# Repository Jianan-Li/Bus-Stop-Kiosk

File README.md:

# Bus-Stop-Kiosk

Click <a href="http://www.jianan.li/bus-stop-kiosk">here</a> for more info on this project.

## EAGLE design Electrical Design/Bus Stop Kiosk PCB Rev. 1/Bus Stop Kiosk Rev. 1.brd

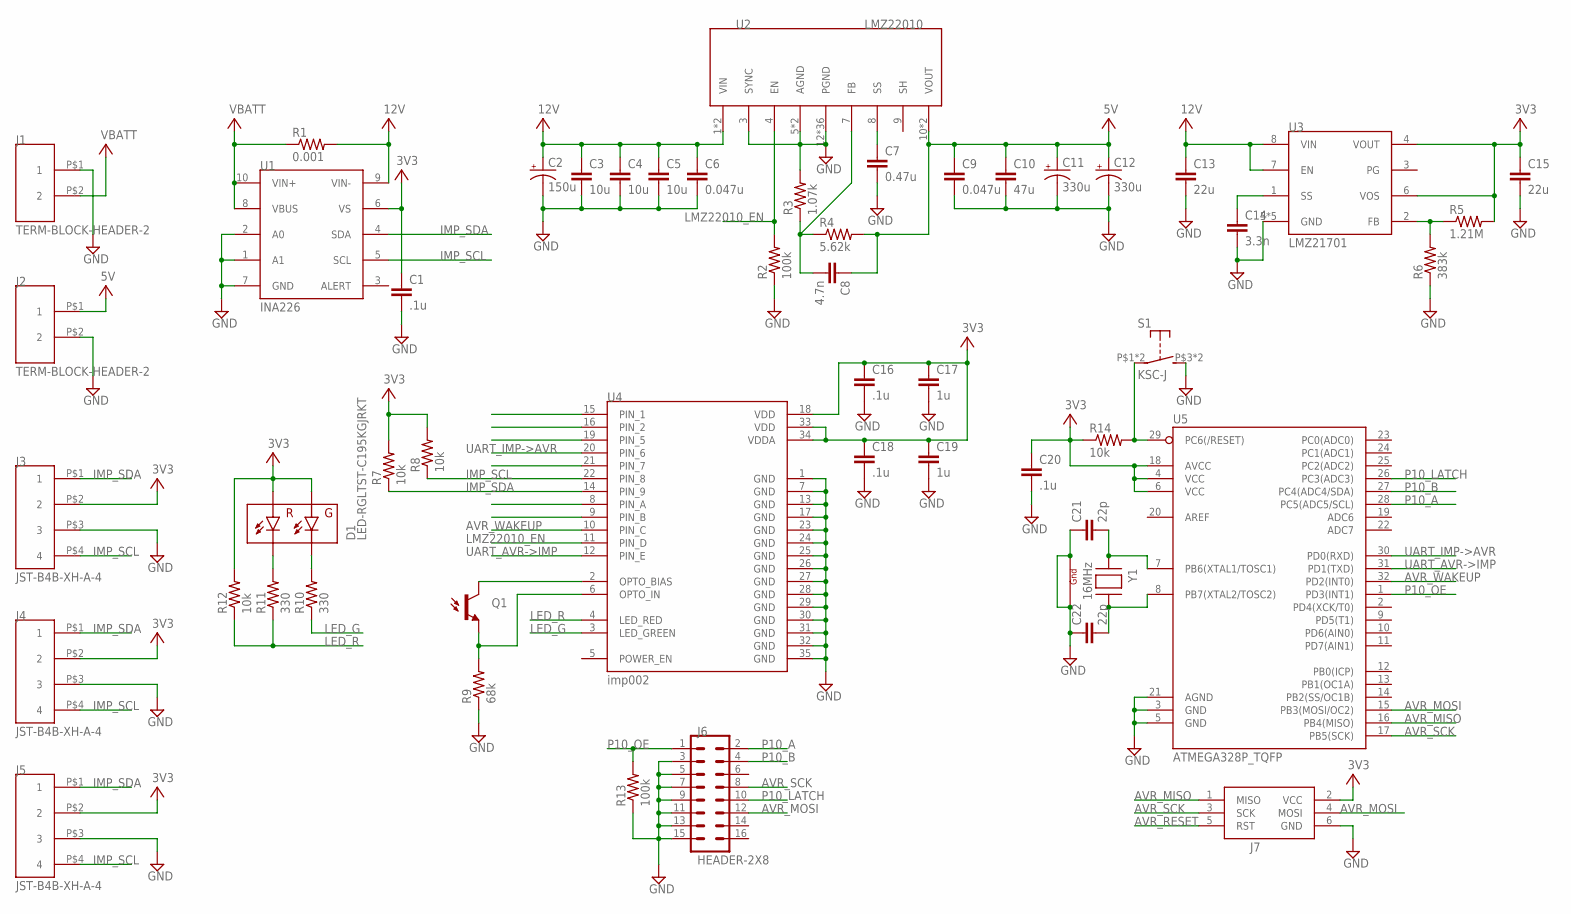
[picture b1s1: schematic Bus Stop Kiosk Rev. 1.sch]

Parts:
C1, C16, C18, C20: .1u; C0603K
C2: 150u; PANASONIC_G
C3, C4, C5: 10u; C1210K
C6, C9: 0.047u; C1206K
C7: 0.47u; C0603K
C8: 4.7n; C0603K
C10: 47u; C1210K
C11, C12: 330u; EIA7343
C13: 22u; C1210K
C14: 3.3n; C0603K
C15: 22u; C0805K
C17, C19: 1u; C0603K
C21, C22: 22p; C0603K
D1: LED-RGLTST-C195KGJRKT; LTST-C195KGJRKT
J1, J2: TERM-BLOCK-HEADER-2; TERM-BLOCK-HDR-2
J3, J4, J5: JST-B4B-XH-A-4
J6: HEADER-2X8; HEADER-2X8-SHROUDED
J7: AVRISP-6; AVRISP
Q1: PHOTOTRANSISTORPT17-21C-L41-TR8; PT17-21C-L41-TR8
R1: 0.001; R1206
R2, R13: 100k; R0603
R3: 1.07k; R0603
R4: 5.62k; R0603
R5: 1.21M; R0603
R6: 383k; R0603
R7, R8, R12, R14: 10k; R0603
R9: 68k; R0603
R10, R11: 330; R0603
S1: KSC-J; C&K-KSC
U1: INA226; VSSOP-10
U2: LMZ22010; TO-PMOD-11
U3: LMZ21701; SIL0008E
U4: imp002; ELECTRIC_IMP_IMP002
U5: ATMEGA328P_TQFP; TQFP32-08
Y1: 16MHz; NX3225

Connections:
3V3: C1.1, C15.1, C16.1, C17.1, C18.1, C19.1, C20.1, D1.P$1 (GA), D1.P$2 (RA), J3.P$2 (2), J4.P$2 (2), J5.P$2 (2), J7.2 (VCC), R5.2, R7.2, R8.2, R12.2, R14.1, U1.6 (VS), U3.4 (VOUT), U3.6 (VOS), U4.18 (VDD), U4.33 (VDD), U4.34 (VDDA), U5.4 (VCC), U5.6 (VCC), U5.18 (AVCC)
5V: C8.1, C9.1, C10.1, C11.A (+), C12.A (+), J2.P$1 (1), R4.2, U2.10 (VOUT), U2.11 (VOUT)
12V: C2.+, C3.1, C4.1, C5.1, C6.1, C13.1, R1.2, U1.9 (VIN-), U2.1 (VIN), U2.2 (VIN), U3.7 (EN), U3.8 (VIN)
ADC1: U4.8 (PIN_A)
ADC2: U4.9 (PIN_B)
AVR_MISO: J7.1 (MISO), U5.16 (PB4(MISO))
AVR_MOSI: J6.12, J7.4 (MOSI), U5.15 (PB3(MOSI/OC2))
AVR_RESET: J7.5 (RST), R14.2, S1.P$1, S1.P$2, U5.29 (PC6(/RESET))
AVR_SCK: J6.8, J7.3 (SCK), U5.17 (PB5(SCK))
AVR_WAKEUP: U4.10 (PIN_C), U5.32 (PD2(INT0))
C21: C21.2, U5.7 (PB6(XTAL1/TOSC1)), Y1.1 (X1)
GND: C1.2, C2.-, C3.2, C4.2, C5.2, C6.2, C7.2, C9.2, C10.2, C11.C (-), C12.C (-), C13.2, C14.2, C15.2, C16.2, C17.2, C18.2, C19.2, C20.2, C21.1, C22.1, J1.P$1 (1), J2.P$2 (2), J3.P$3 (3), J4.P$3 (3), J5.P$3 (3), J6.3, J6.5, J6.7, J6.9, J6.11, J6.13, J6.15, J7.6 (GND), R2.1, R3.2, R6.1, R9.1, R13.1, S1.P$3 (S), S1.P$4 (S), U1.1 (A1), U1.2 (A0), U1.7 (GND), U2.3 (SYNC), U2.5 (AGND), U2.6 (AGND), U2.12 (PGND), U2.P$1 (PGND), U2.P$2 (PGND), U2.P$3 (PGND), U2.P$4 (PGND), U2.P$5 (PGND), U2.P$6 (PGND), U2.P$7 (PGND), U2.P$8 (PGND), U2.P$9 (PGND), U2.P$10 (PGND), U2.P$11 (PGND), U2.P$12 (PGND), U2.P$13 (PGND), U2.P$14 (PGND), U2.P$15 (PGND), U2.P$16 (PGND), U2.P$17 (PGND), U2.P$18 (PGND), U2.P$19 (PGND), U2.P$20 (PGND), U2.P$21 (PGND), U2.P$22 (PGND), U2.P$23 (PGND), U2.P$24 (PGND), U2.P$25 (PGND), U2.P$26 (PGND), U2.P$27 (PGND), U2.P$28 (PGND), U2.P$29 (PGND), U2.P$30 (PGND), U2.P$31 (PGND), U2.P$32 (PGND), U2.P$33 (PGND), U2.P$34 (PGND), U2.P$35 (PGND), U3.5 (GND), U3.9 (GND), U3.10 (GND), U3.11 (GND), U3.12 (GND), U4.1 (GND), U4.7 (GND), U4.13 (GND), U4.17 (GND), U4.23 (GND), U4.24 (GND), U4.25 (GND), U4.26 (GND), U4.27 (GND), U4.28 (GND), U4.29 (GND), U4.30 (GND), U4.31 (GND), U4.32 (GND), U4.35 (GND), U5.3 (GND), U5.5 (GND), U5.21 (AGND), Y1.2 (G2), Y1.4 (G1)
IMP_SCL: J3.P$4 (4), J4.P$4 (4), J5.P$4 (4), R8.1, U1.5 (SCL), U4.22 (PIN_8)
IMP_SDA: J3.P$1 (1), J4.P$1 (1), J5.P$1 (1), R7.1, U1.4 (SDA), U4.14 (PIN_9)
LED_G: R10.1, U4.3 (LED_GREEN)
LED_R: R11.1, R12.1, U4.4 (LED_RED)
LMZ22010_EN: R2.2, U2.4 (EN), U4.11 (PIN_D)
unnamed: Q1.C, U4.2 (OPTO_BIAS)
unnamed: Q1.E, R9.2, U4.6 (OPTO_IN)
unnamed: D1.P$3 (GC), R10.2
unnamed: D1.P$4 (RC), R11.2
unnamed: C14.1, U3.1 (SS)
unnamed: C8.2, R3.1, R4.1, U2.7 (FB)
unnamed: C7.1, U2.8 (SS)
unnamed: R5.1, R6.2, U3.2 (FB)
unnamed: C22.2, U5.8 (PB7(XTAL2/TOSC2)), Y1.3 (X2)
P10_A: J6.2, U5.28 (PC5(ADC5/SCL))
P10_B: J6.4, U5.27 (PC4(ADC4/SDA))
P10_LATCH: J6.10, U5.26 (PC3(ADC3))
P10_OE: J6.1, R13.2, U5.1 (PD3(INT1))
UART_AVR->IMP: U4.12 (PIN_E), U5.31 (PD1(TXD))
UART_IMP->AVR: U4.20 (PIN_6), U5.30 (PD0(RXD))
VBATT: J1.P$2 (2), R1.1, U1.8 (VBUS), U1.10 (VIN+)

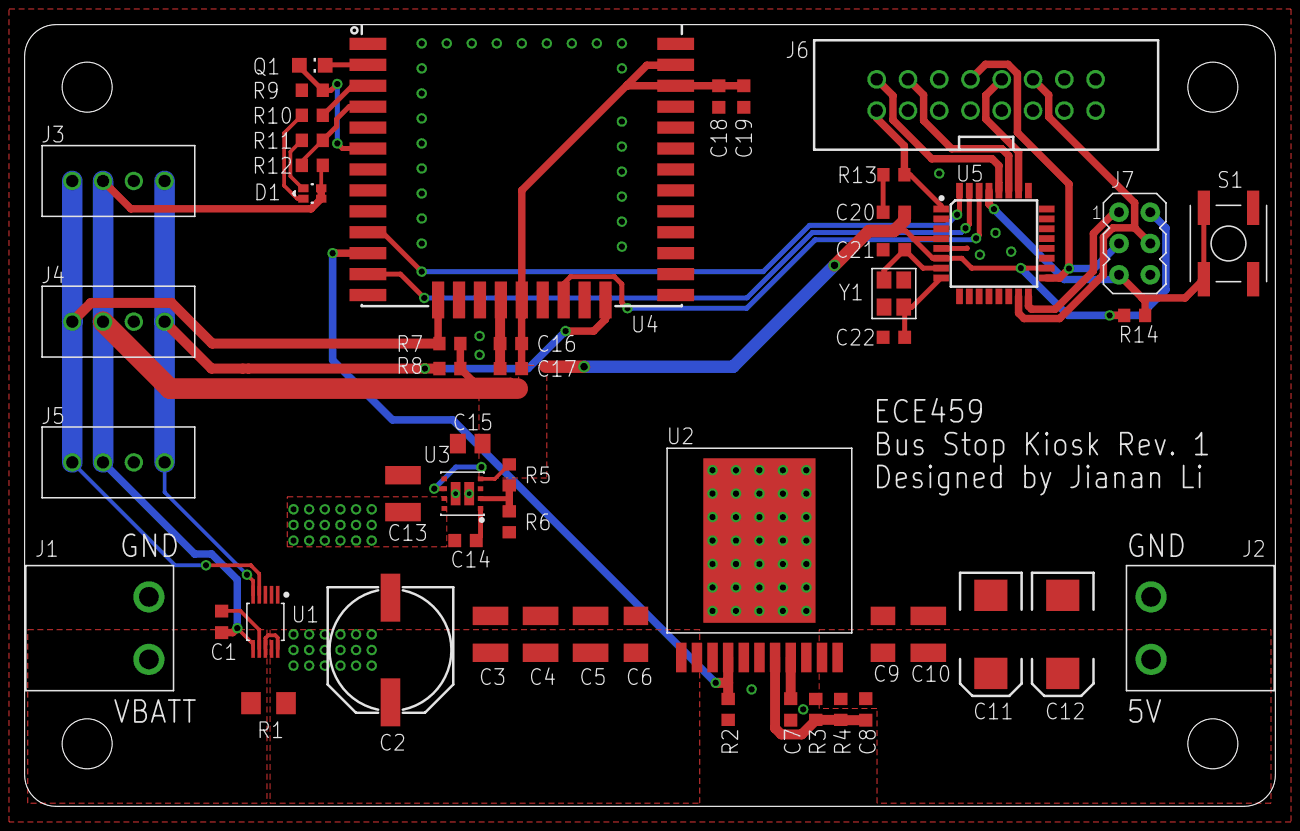
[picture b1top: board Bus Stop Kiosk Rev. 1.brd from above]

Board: 2 copper layers, 101.6 x 63.5 mm, 52 parts (0 on the bottom side), 31 nets.

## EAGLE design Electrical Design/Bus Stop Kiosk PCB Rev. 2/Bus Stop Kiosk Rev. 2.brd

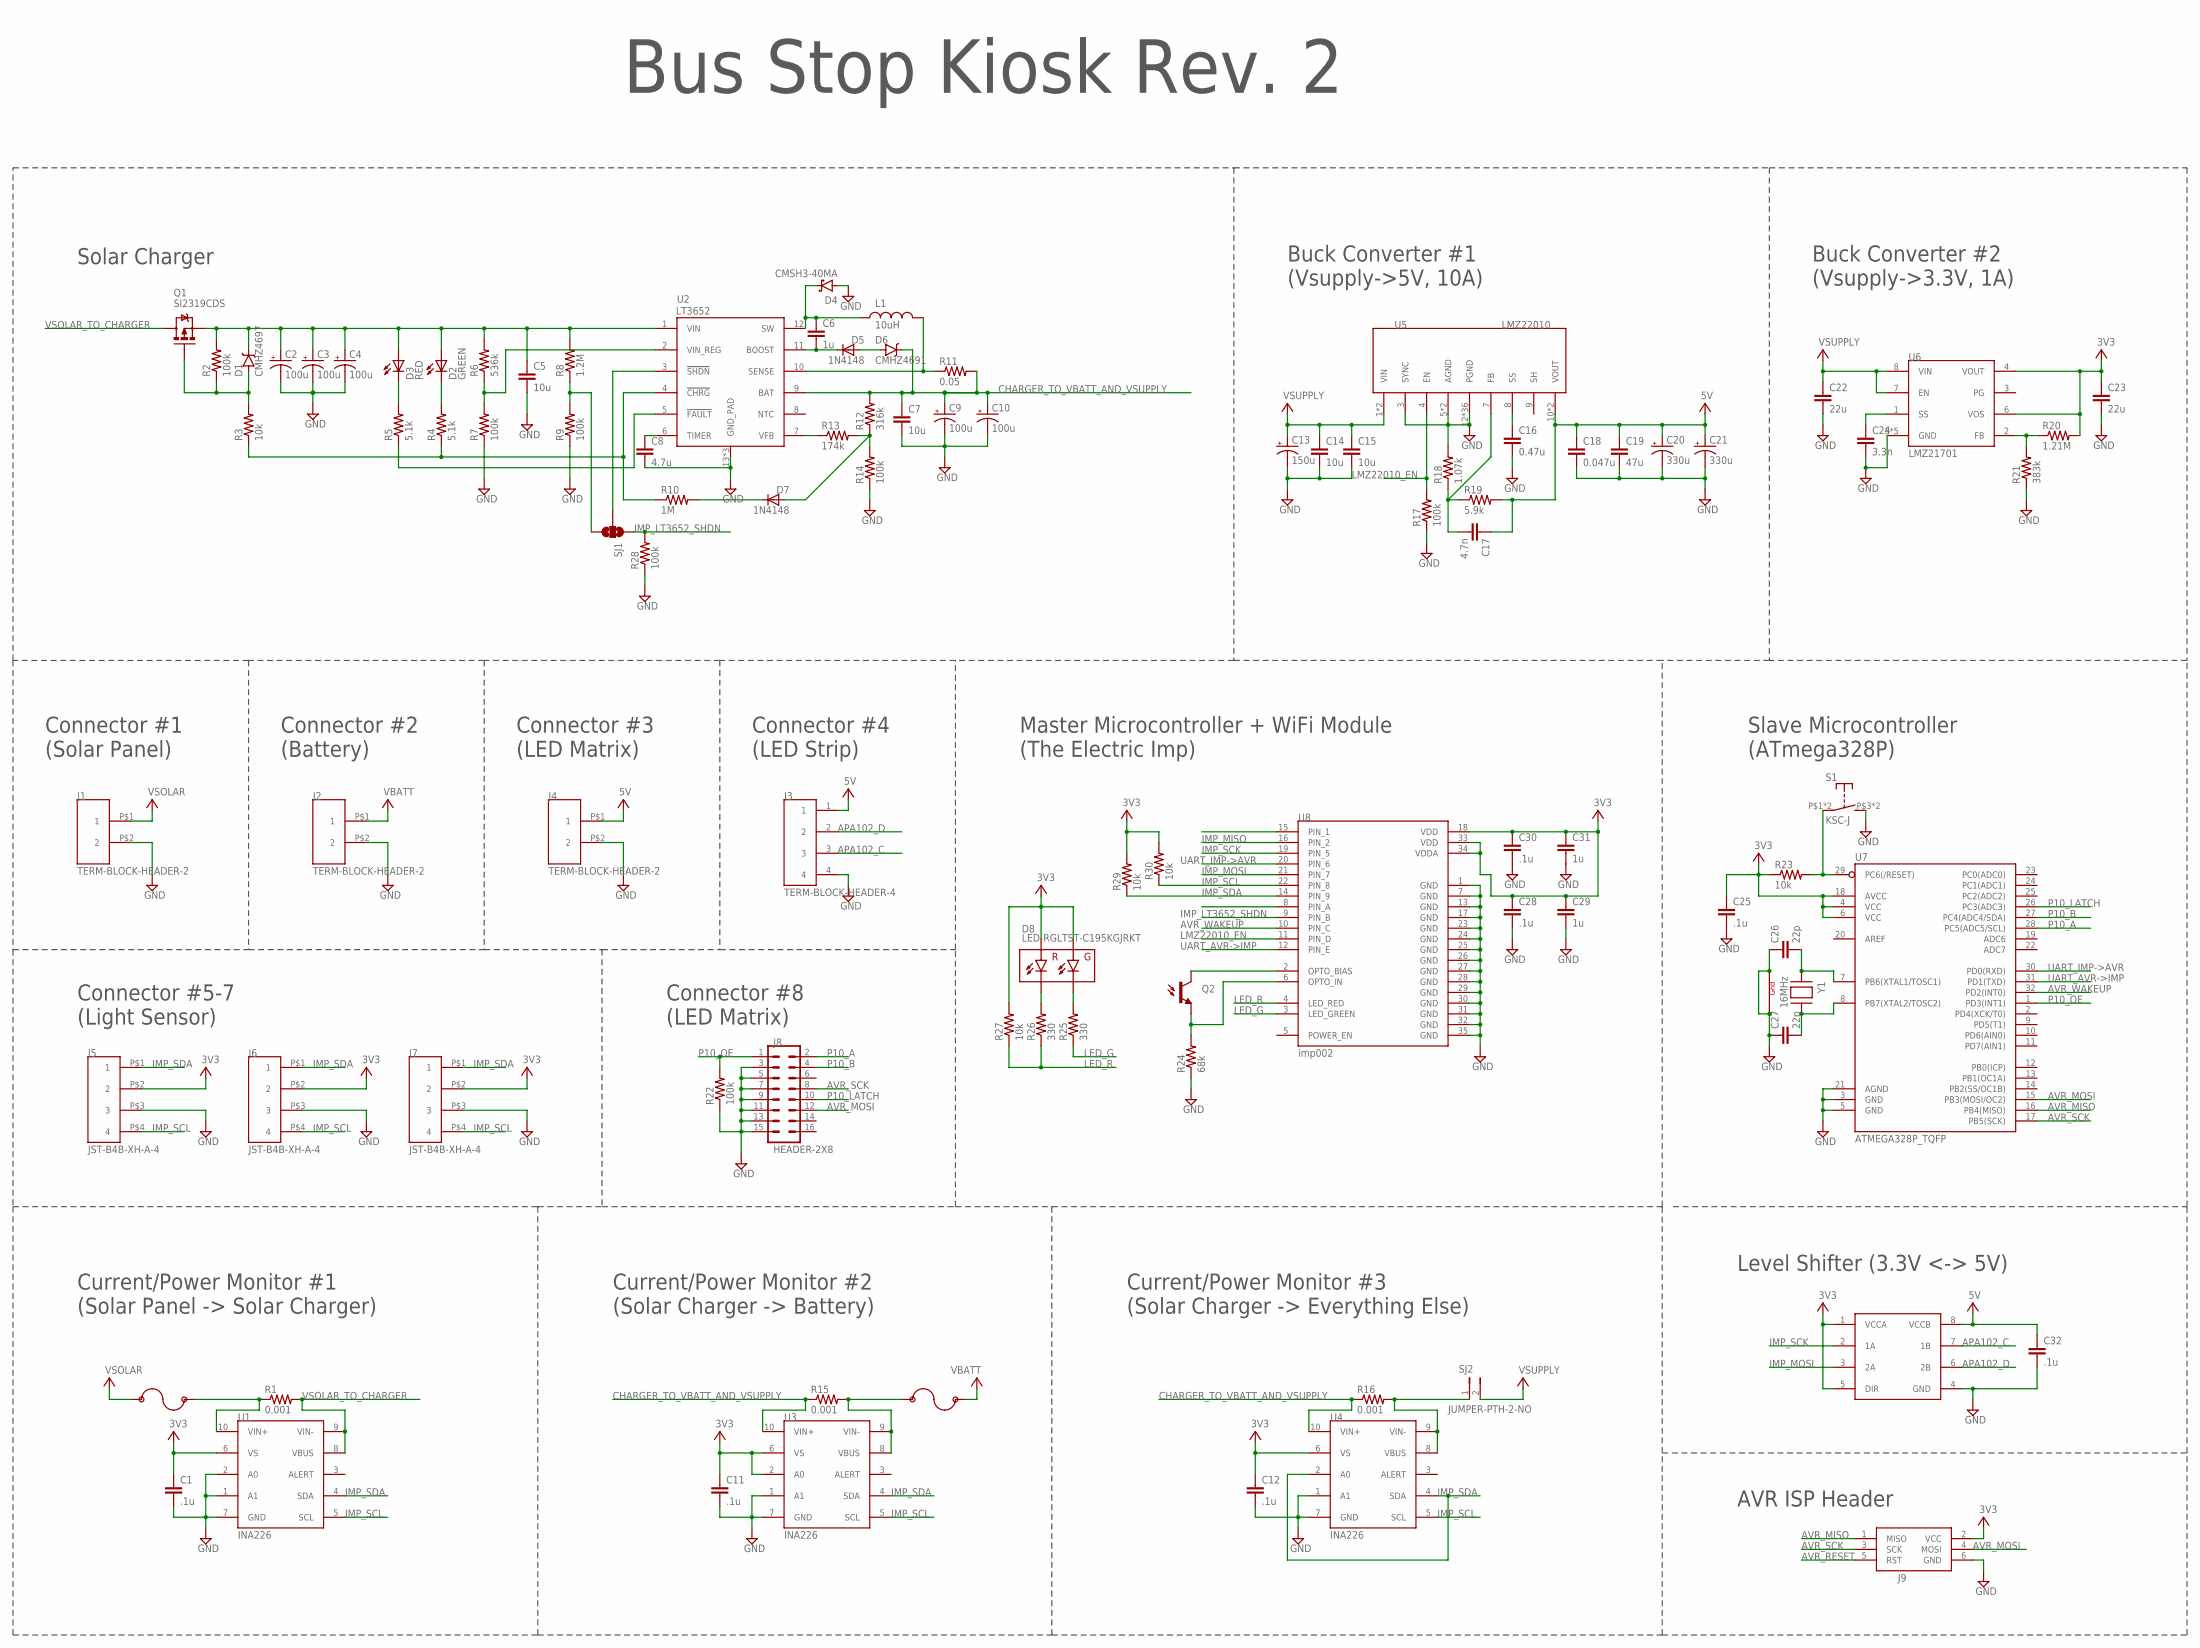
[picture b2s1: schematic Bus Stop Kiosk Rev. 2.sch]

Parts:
C1, C11, C12, C25, C28, C30, C32: .1u; C0603K
C2, C3, C4, C9, C10: 100u; EIA7343
C5, C7, C14, C15: 10u; C1210K
C6: 1u; C0805K
C8: 4.7u; C0603K
C13: 150u; PANASONIC_G
C16: 0.47u; C0603K
C17: 4.7n; C0603K
C18: 0.047u; C1206K
C19: 47u; C1210K
C20, C21: 330u; EIA7343
C22: 22u; C1210K
C23: 22u; C0805K
C24: 3.3n; C0603K
C26, C27: 22p; C0603K
C29, C31: 1u; C0603K
D1: CMHZ4697; SOD-123
D2: GREEN; CHIP-LED0603
D3: RED; CHIP-LED0603
D4: CMSH3-40MA; SMA-DIODE
D5, D7: 1N4148; SOD-123
D6: CMHZ4691; SOD-123
D8: LED-RGLTST-C195KGJRKT; LTST-C195KGJRKT
F1, F2: 4A; 0603
J1, J2, J4: TERM-BLOCK-HEADER-2; TERM-BLOCK-HDR-2
J3: TERM-BLOCK-HEADER-4; OSTOQ045451
J5, J6, J7: JST-B4B-XH-A-4
J8: HEADER-2X8; HEADER-2X8-SHROUDED
J9: AVRISP-6; AVRISP
L1: 10uH; INDUCTOR-6.86X6.47
Q1: SI2319CDS; SOT-23-3
Q2: PHOTOTRANSISTORPT17-21C-L41-TR8; PT17-21C-L41-TR8
R1, R15, R16: 0.001; R1206
R2, R14, R17, R22, R28: 100k; R0603
R3, R23, R27, R29, R30: 10k; R0603
R4, R5: 5.1k; R0402
R6: 536k; R0402
R7, R9: 100k; R0402
R8: 1.2M; R0402
R10: 1M; R0402
R11: 0.05; R1206
R12: 316k; R0603
R13: 174k; R0402
R18: 1.07k; R0603
R19: 5.9k; R0603
R20: 1.21M; R0603
R21: 383k; R0603
R24: 68k; R0603
R25, R26: 330; R0603
S1: KSC-J; C&K-KSC
SJ1: JUMPER-PAD-3-NOYES_SILK; PAD-JUMPER-3-NO_YES_SILK
SJ2: JUMPER-PTH-2-NO; PTH-JUMPER-2-NO_NO_SILK
U1, U3, U4: INA226; VSSOP-10
U2: LT3652; MSOP-12_GND
U5: LMZ22010; TO-PMOD-11
U6: LMZ21701; SIL0008E
U7: ATMEGA328P_TQFP; TQFP32-08
U8: imp002; ELECTRIC_IMP_IMP002
U9: 74LVC2T45; VSSOP-8
Y1: 16MHz; NX3225

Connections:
3V3: C1.1, C11.1, C12.1, C23.1, C25.1, C28.1, C29.1, C30.1, C31.1, D8.P$1 (GA), D8.P$2 (RA), J5.P$2 (2), J6.P$2 (2), J7.P$2 (2), J9.2 (VCC), R20.2, R23.1, R27.2, R29.2, R30.2, U1.6 (VS), U3.2 (A0), U3.6 (VS), U4.6 (VS), U6.4 (VOUT), U6.6 (VOS), U7.4 (VCC), U7.6 (VCC), U7.18 (AVCC), U8.18 (VDD), U8.33 (VDD), U8.34 (VDDA), U9.1 (VCCA), U9.5 (DIR)
5V: C17.1, C18.1, C19.1, C20.A (+), C21.A (+), C32.1, J3.1, J4.P$1 (1), R19.2, U5.10 (VOUT), U5.11 (VOUT), U9.8 (VCCB)
ADC1: U8.8 (PIN_A)
APA102_C: J3.3, U9.7 (1B)
APA102_D: J3.2, U9.6 (2B)
AVR_MISO: J9.1 (MISO), U7.16 (PB4(MISO))
AVR_MOSI: J8.12, J9.4 (MOSI), U7.15 (PB3(MOSI/OC2))
AVR_RESET: J9.5 (RST), R23.2, S1.P$1, S1.P$2, U7.29 (PC6(/RESET))
AVR_SCK: J8.8, J9.3 (SCK), U7.17 (PB5(SCK))
AVR_WAKEUP: U7.32 (PD2(INT0)), U8.10 (PIN_C)
BOOST: C6.2, D5.C, U2.11 (BOOST)
C21: C26.2, U7.7 (PB6(XTAL1/TOSC1)), Y1.1 (X1)
CHARGER_TO_VBATT_AND_VSUPPLY: C7.1, C9.A (+), C10.A (+), D6.C, R11.2, R12.2, R15.1, R16.1, U2.9 (BAT), U3.10 (VIN+), U4.10 (VIN+)
CHRG: R3.1, R4.1, R10.1, U2.4 (!CHRG)
FAULT: R5.1, U2.5 (!FAULT)
GND: C1.2, C2.C (-), C3.C (-), C4.C (-), C5.2, C7.2, C8.2, C9.C (-), C10.C (-), C11.2, C12.2, C13.-, C14.2, C15.2, C16.2, C18.2, C19.2, C20.C (-), C21.C (-), C22.2, C23.2, C24.2, C25.2, C26.1, C27.1, C28.2, C29.2, C30.2, C31.2, C32.2, D4.A, J1.P$2 (2), J2.P$2 (2), J3.4, J4.P$2 (2), J5.P$3 (3), J6.P$3 (3), J7.P$3 (3), J8.3, J8.5, J8.7, J8.9, J8.11, J8.13, J8.15, J9.6 (GND), R7.1, R9.1, R14.1, R17.1, R18.2, R21.1, R22.1, R24.1, R28.1, S1.P$3 (S), S1.P$4 (S), U1.1 (A1), U1.2 (A0), U1.7 (GND), U2.13 (GND_PAD), U2.P$1 (GND_PAD), U2.P$2 (GND_PAD), U3.1 (A1), U3.7 (GND), U4.1 (A1), U4.7 (GND), U5.3 (SYNC), U5.5 (AGND), U5.6 (AGND), U5.12 (PGND), U5.P$1 (PGND), U5.P$2 (PGND), U5.P$3 (PGND), U5.P$4 (PGND), U5.P$5 (PGND), U5.P$6 (PGND), U5.P$7 (PGND), U5.P$8 (PGND), U5.P$9 (PGND), U5.P$10 (PGND), U5.P$11 (PGND), U5.P$12 (PGND), U5.P$13 (PGND), U5.P$14 (PGND), U5.P$15 (PGND), U5.P$16 (PGND), U5.P$17 (PGND), U5.P$18 (PGND), U5.P$19 (PGND), U5.P$20 (PGND), U5.P$21 (PGND), U5.P$22 (PGND), U5.P$23 (PGND), U5.P$24 (PGND), U5.P$25 (PGND), U5.P$26 (PGND), U5.P$27 (PGND), U5.P$28 (PGND), U5.P$29 (PGND), U5.P$30 (PGND), U5.P$31 (PGND), U5.P$32 (PGND), U5.P$33 (PGND), U5.P$34 (PGND), U5.P$35 (PGND), U6.5 (GND), U6.9 (GND), U6.10 (GND), U6.11 (GND), U6.12 (GND), U7.3 (GND), U7.5 (GND), U7.21 (AGND), U8.1 (GND), U8.7 (GND), U8.13 (GND), U8.17 (GND), U8.23 (GND), U8.24 (GND), U8.25 (GND), U8.26 (GND), U8.27 (GND), U8.28 (GND), U8.29 (GND), U8.30 (GND), U8.31 (GND), U8.32 (GND), U8.35 (GND), U9.4 (GND), Y1.2 (G2), Y1.4 (G1)
IMP_LT3652_SHDN: R28.2, SJ1.1, U8.9 (PIN_B)
IMP_MISO: U8.16 (PIN_2)
IMP_MOSI: U8.21 (PIN_7), U9.3 (2A)
IMP_SCK: U8.19 (PIN_5), U9.2 (1A)
IMP_SCL: J5.P$4 (4), J6.P$4 (4), J7.P$4 (4), R30.1, U1.5 (SCL), U3.5 (SCL), U4.5 (SCL), U8.22 (PIN_8)
IMP_SDA: J5.P$1 (1), J6.P$1 (1), J7.P$1 (1), R29.1, U1.4 (SDA), U3.4 (SDA), U4.2 (A0), U4.4 (SDA), U8.14 (PIN_9)
LED_G: R25.1, U8.3 (LED_GREEN)
LED_R: R26.1, R27.1, U8.4 (LED_RED)
LMZ22010_EN: R17.2, U5.4 (EN), U8.11 (PIN_D)
unnamed: Q2.C, U8.2 (OPTO_BIAS)
unnamed: Q2.E, R24.2, U8.6 (OPTO_IN)
unnamed: D8.P$3 (GC), R25.2
unnamed: D8.P$4 (RC), R26.2
unnamed: C24.1, U6.1 (SS)
unnamed: D7.C, R10.2
unnamed: C17.2, R18.1, R19.1, U5.7 (FB)
unnamed: C16.1, U5.8 (SS)
unnamed: R20.1, R21.2, U6.2 (FB)
unnamed: R8.1, R9.2, SJ1.3
unnamed: D7.A, R12.1, R13.2, R14.2
unnamed: D3.C, R5.2
unnamed: D1.A, Q1.1 (G), R2.1, R3.2
unnamed: D2.C, R4.2
unnamed: C27.2, U7.8 (PB7(XTAL2/TOSC2)), Y1.3 (X2)
unnamed: D5.A, D6.A
unnamed: F1.2, R1.1, U1.10 (VIN+)
unnamed: R16.2, SJ2.1, U4.8 (VBUS), U4.9 (VIN-)
unnamed: F2.1, R15.2, U3.8 (VBUS), U3.9 (VIN-)
P10_A: J8.2, U7.28 (PC5(ADC5/SCL))
P10_B: J8.4, U7.27 (PC4(ADC4/SDA))
P10_LATCH: J8.10, U7.26 (PC3(ADC3))
P10_OE: J8.1, R22.2, U7.1 (PD3(INT1))
SENSE: L1.P$2 (2), R11.1, U2.10 (SENSE)
SHDN: SJ1.2, U2.3 (!SHDN)
SW: C6.1, D4.C, L1.P$1 (1), U2.12 (SW)
TIMER: C8.1, U2.6 (TIMER)
UART_AVR->IMP: U7.31 (PD1(TXD)), U8.12 (PIN_E)
UART_IMP->AVR: U7.30 (PD0(RXD)), U8.20 (PIN_6)
VBATT: F2.2, J2.P$1 (1)
VFB: R13.1, U2.7 (VFB)
VIN: C2.A (+), C3.A (+), C4.A (+), C5.1, D1.C, D2.A, D3.A, Q1.2 (S), R2.2, R6.2, R8.2, U2.1 (VIN)
VIN_REG: R6.1, R7.2, U2.2 (VIN_REG)
VSOLAR: F1.1, J1.P$1 (1)
VSOLAR_TO_CHARGER: Q1.3 (D), R1.2, U1.8 (VBUS), U1.9 (VIN-)
VSUPPLY: C13.+, C14.1, C15.1, C22.1, SJ2.2, U5.1 (VIN), U5.2 (VIN), U6.7 (EN), U6.8 (VIN)

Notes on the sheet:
Solar Charger
Current/Power Monitor #1 (Solar Panel -> Solar Charger)
Current/Power Monitor #2 (Solar Charger -> Battery)
Current/Power Monitor #3 (Solar Charger -> Everything Else)
Buck Converter #1 (Vsupply->5V, 10A)
Connector #1 (Solar Panel)
Connector #2 (Battery)
Connector #3 (LED Matrix)
Connector #4 (LED Strip)
Buck Converter #2 (Vsupply->3.3V, 1A)
Master Microcontroller + WiFi Module (The Electric Imp)
Connector #5-7 (Light Sensor)
Level Shifter (3.3V <-> 5V)
Connector #8 (LED Matrix)
Slave Microcontroller (ATmega328P)
AVR ISP Header
Bus Stop Kiosk Rev. 2

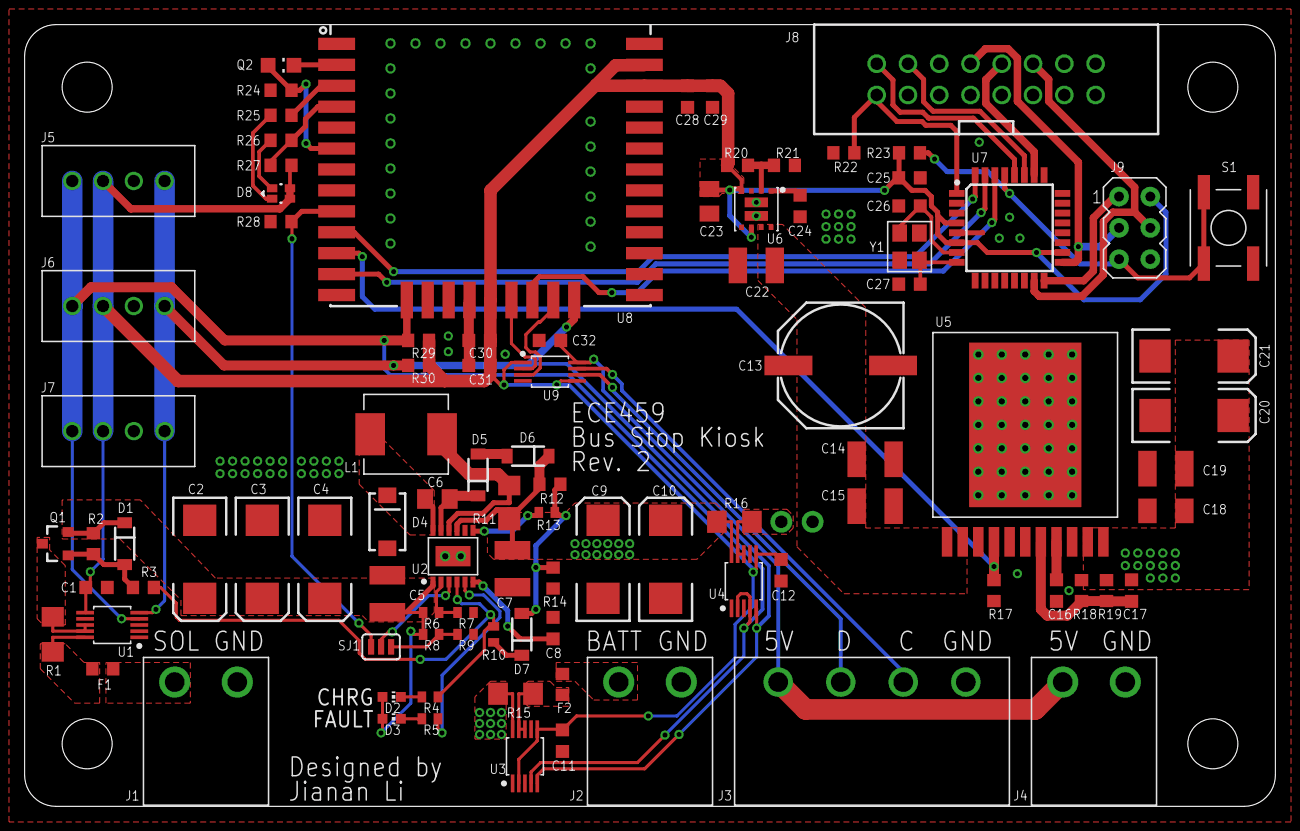
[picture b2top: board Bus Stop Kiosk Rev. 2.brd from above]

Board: 2 copper layers, 101.6 x 63.5 mm, 97 parts (0 on the bottom side), 59 nets.

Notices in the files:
parts and their libraries:
SparkFun-DigitalIC: Licensing: Creative Commons ShareAlike 4.0 International - https://creativecommons.org/licenses/by-sa/4.0
